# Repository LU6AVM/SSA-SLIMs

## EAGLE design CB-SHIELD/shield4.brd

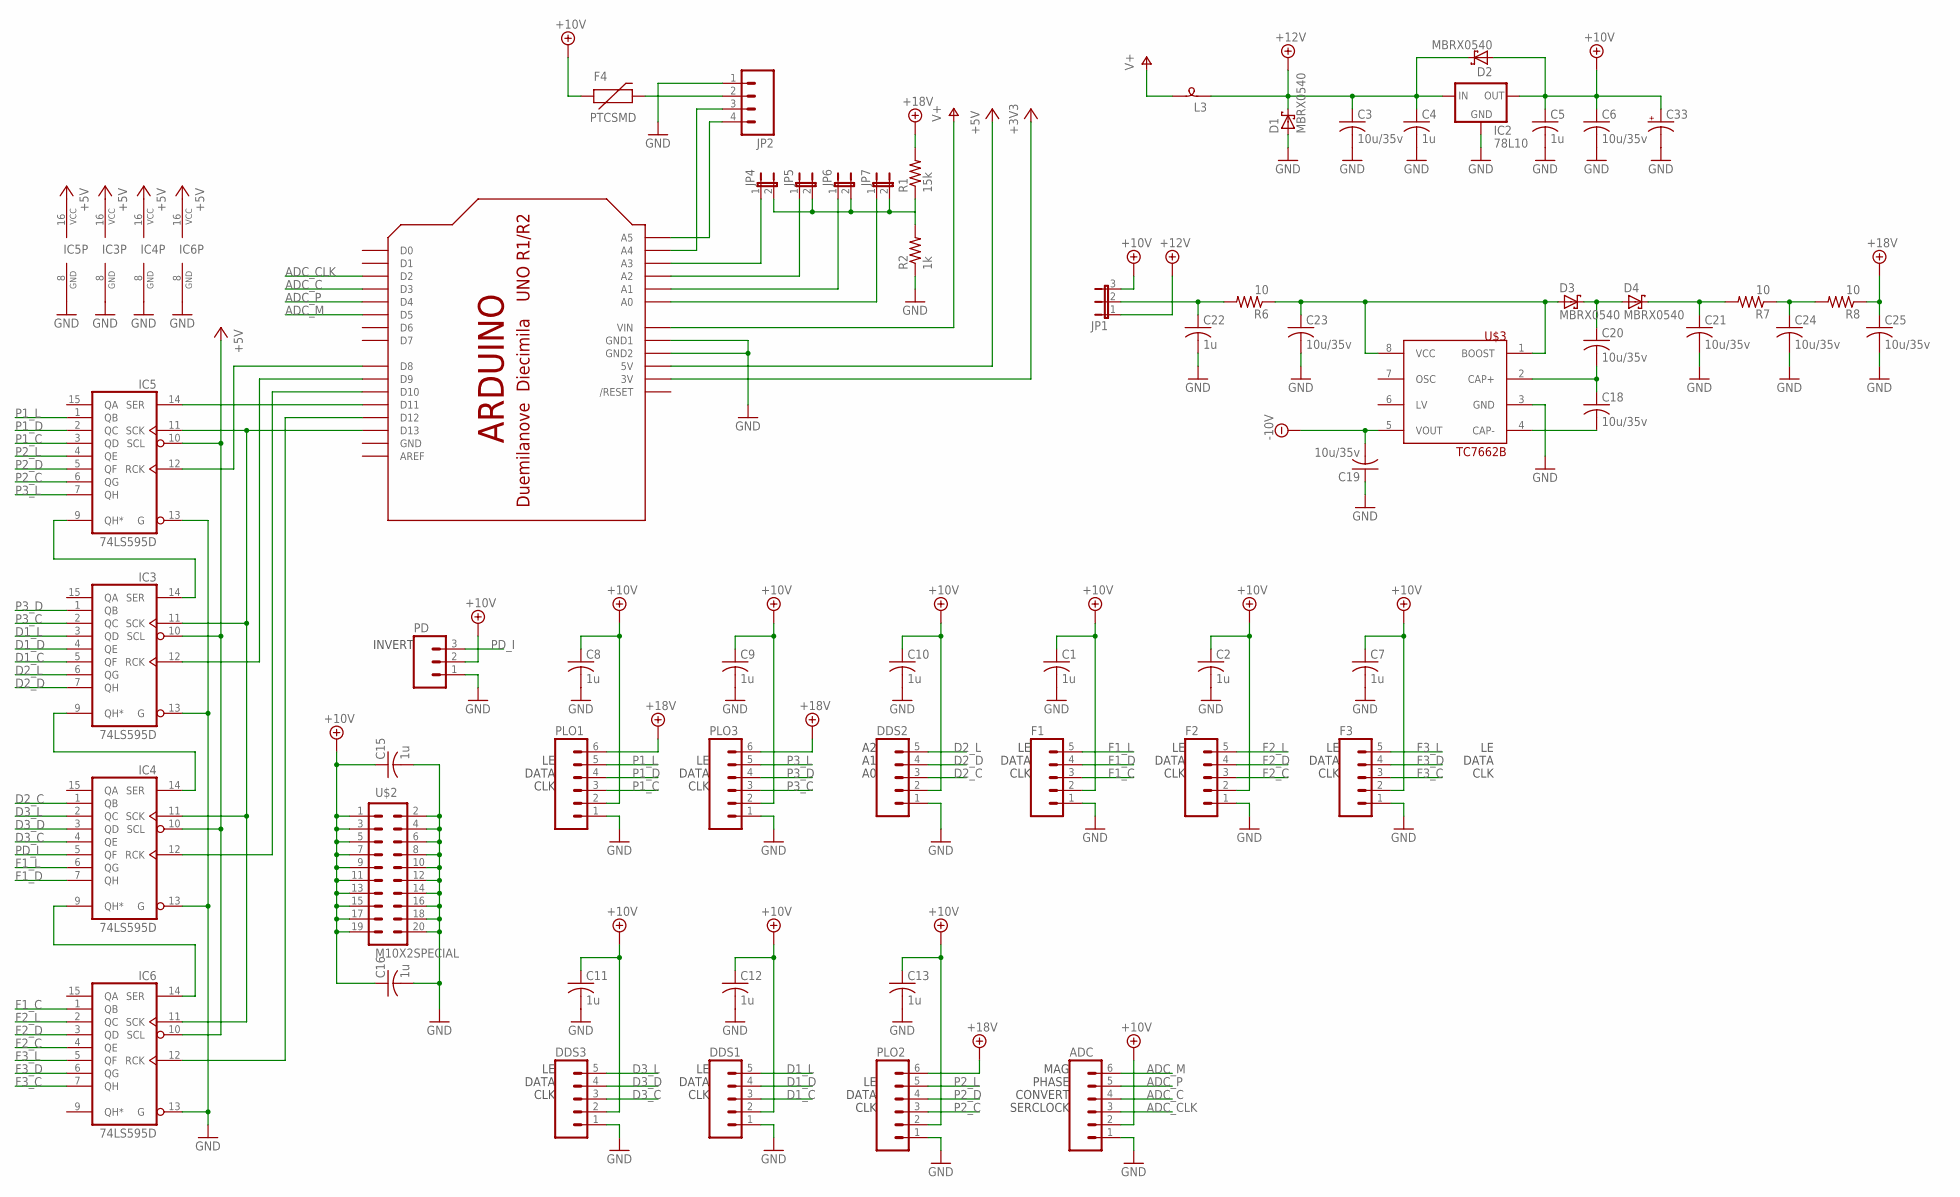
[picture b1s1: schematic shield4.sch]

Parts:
ADC: M06LOCK; 1X06_LOCK
C1, C2, C4, C5, C7, C8, C9, C10, C11, C12, C13, C15, C16, C22: 1u; C0603
C3, C6, C18, C19, C20, C21, C23, C24, C25: 10u/35v; C1206
C33: CPOL-USE2.5-6; E2,5-6
D1, D2, D3, D4: MBRX0540; SOD323-R
DDS1, DDS2, DDS3: M05LOCK; 1X05_LOCK
F1, F2, F3: M05LOCK; 1X05_LOCK
F4: PTCSMD; PTC-1206
IC2: 78L10; 78XXS
IC3, IC4, IC5, IC6: 74LS595D; SO16
JP1: JP2E; JP2
JP2: M04LOCK; 1X04_LOCK
JP4, JP5, JP6, JP7: JUMPER-2SMD-NO; SJ_2S-NO
L3: SM-B5
PD: M03LOCK; 1X03_LOCK
PLO1, PLO2, PLO3: M06LOCK; 1X06_LOCK
R1: 15k; R0603
R2: 1k; R0603
R6, R7, R8: 10; R0603
U$1: ARDUINO-NOHOLE
U$2: M10X2SPECIAL; 2X10_LOCK_SPECIAL
U$3: TC7662B; SO-08

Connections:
+3V3: U$1.3V
+5V: IC3.10 (SCL), IC3.16 (VCC), IC4.10 (SCL), IC4.16 (VCC), IC5.10 (SCL), IC5.16 (VCC), IC6.10 (SCL), IC6.16 (VCC), U$1.5V
+10V: ADC.2, C1.1, C2.1, C5.1, C6.1, C7.1, C8.1, C9.1, C10.1, C11.1, C12.1, C13.1, C15.1, C16.1, C33.+, D2.A, DDS1.2, DDS2.2, DDS3.2, F1.2, F2.2, F3.2, F4.1, IC2.OUT, JP1.3, PD.2, PLO1.2, PLO2.2, PLO3.2, U$2.1, U$2.3, U$2.5, U$2.7, U$2.9, U$2.11, U$2.13, U$2.15, U$2.17, U$2.19
+12V: C3.1, C4.1, D1.C, D2.C, IC2.IN, JP1.1, L3.1
+18V: C25.1, PLO1.6, PLO2.6, PLO3.6, R1.2, R8.1
-10V: C19.2, U$3.5 (VOUT)
ADC_C: ADC.4, U$1.D3
ADC_CLK: ADC.3, U$1.D2
ADC_M: ADC.6, U$1.D5
ADC_P: ADC.5, U$1.D4
D1_C: DDS1.3, IC3.5 (QF)
D1_D: DDS1.4, IC3.4 (QE)
D1_L: DDS1.5, IC3.3 (QD)
D2_C: DDS2.3, IC4.1 (QB)
D2_D: DDS2.4, IC3.7 (QH)
D2_L: DDS2.5, IC3.6 (QG)
D3_C: DDS3.3, IC4.4 (QE)
D3_D: DDS3.4, IC4.3 (QD)
D3_L: DDS3.5, IC4.2 (QC)
F1_C: F1.3, IC6.1 (QB)
F1_D: F1.4, IC4.7 (QH)
F1_L: F1.5, IC4.6 (QG)
F2_C: F2.3, IC6.4 (QE)
F2_D: F2.4, IC6.3 (QD)
F2_L: F2.5, IC6.2 (QC)
F3_C: F3.3, IC6.7 (QH)
F3_D: F3.4, IC6.6 (QG)
F3_L: F3.5, IC6.5 (QF)
GND: ADC.1, C1.2, C2.2, C3.2, C4.2, C5.2, C6.2, C7.2, C8.2, C9.2, C10.2, C11.2, C12.2, C13.2, C15.2, C16.2, C19.1, C21.2, C22.2, C23.2, C24.2, C25.2, C33.-, D1.A, DDS1.1, DDS2.1, DDS3.1, F1.1, F2.1, F3.1, IC2.GND, IC3.8 (GND), IC3.13 (G), IC4.8 (GND), IC4.13 (G), IC5.8 (GND), IC5.13 (G), IC6.8 (GND), IC6.13 (G), JP2.1, PD.1, PLO1.1, PLO2.1, PLO3.1, R2.1, U$1.GND, U$1.GND1, U$1.GND2, U$2.2, U$2.4, U$2.6, U$2.8, U$2.10, U$2.12, U$2.14, U$2.16, U$2.18, U$2.20, U$3.3 (GND)
unnamed: IC5.14 (SER), U$1.D11
unnamed: IC3.11 (SCK), IC4.11 (SCK), IC5.11 (SCK), IC6.11 (SCK), U$1.D13
unnamed: IC5.12 (RCK), U$1.D8
unnamed: IC3.14 (SER), IC5.9 (QH*)
unnamed: IC3.9 (QH*), IC4.14 (SER)
unnamed: IC4.9 (QH*), IC6.14 (SER)
unnamed: JP2.3, U$1.A4
unnamed: JP2.4, U$1.A5
unnamed: F4.2, JP2.2
unnamed: JP4.1, U$1.A3
unnamed: JP5.1, U$1.A2
unnamed: JP6.1, U$1.A1
unnamed: JP7.1, U$1.A0
unnamed: JP4.2, JP5.2, JP6.2, JP7.2, R1.1, R2.2
unnamed: IC6.12 (RCK), U$1.D12
unnamed: IC4.12 (RCK), U$1.D10
unnamed: IC3.12 (RCK), U$1.D9
unnamed: C22.1, JP1.2, R6.2
unnamed: C23.1, D3.A, R6.1, U$3.1 (BOOST), U$3.8 (VCC)
unnamed: C18.2, U$3.4 (CAP-)
unnamed: C18.1, C20.2, U$3.2 (CAP+)
unnamed: C20.1, D3.C, D4.A
unnamed: C21.1, D4.C, R7.2
unnamed: C24.1, R7.1, R8.2
P1_C: IC5.3 (QD), PLO1.3
P1_D: IC5.2 (QC), PLO1.4
P1_L: IC5.1 (QB), PLO1.5
P2_C: IC5.6 (QG), PLO2.3
P2_D: IC5.5 (QF), PLO2.4
P2_L: IC5.4 (QE), PLO2.5
P3_C: IC3.2 (QC), PLO3.3
P3_D: IC3.1 (QB), PLO3.4
P3_L: IC5.7 (QH), PLO3.5
PD_I: IC4.5 (QF), PD.3
V+: L3.2, U$1.VIN

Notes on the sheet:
SERCLOCK
CONVERT
PHASE
MAG
CLK
DATA
INVERT

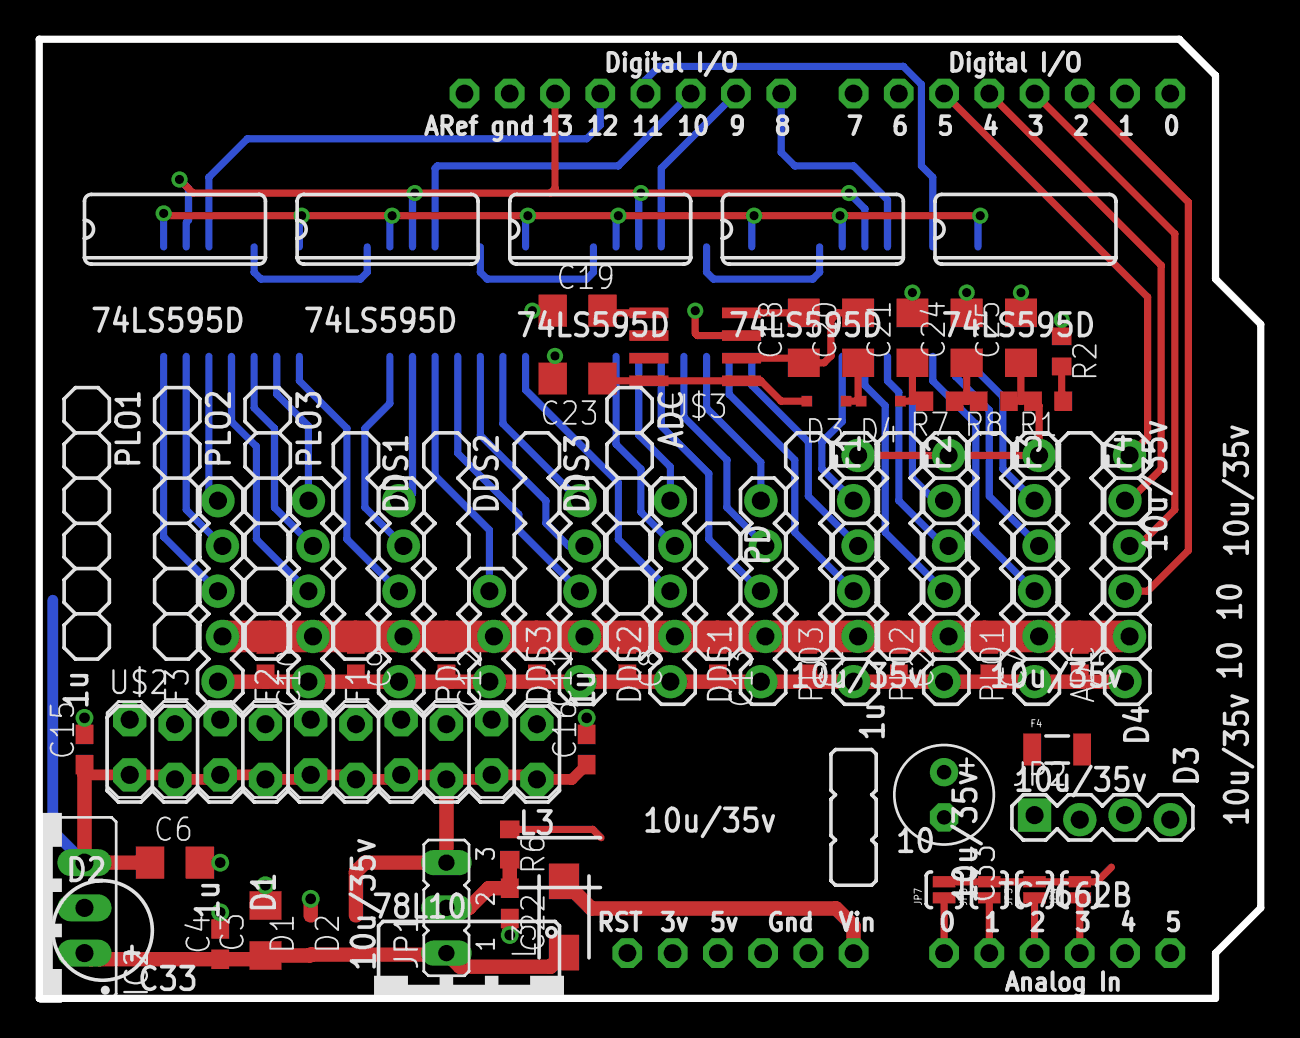
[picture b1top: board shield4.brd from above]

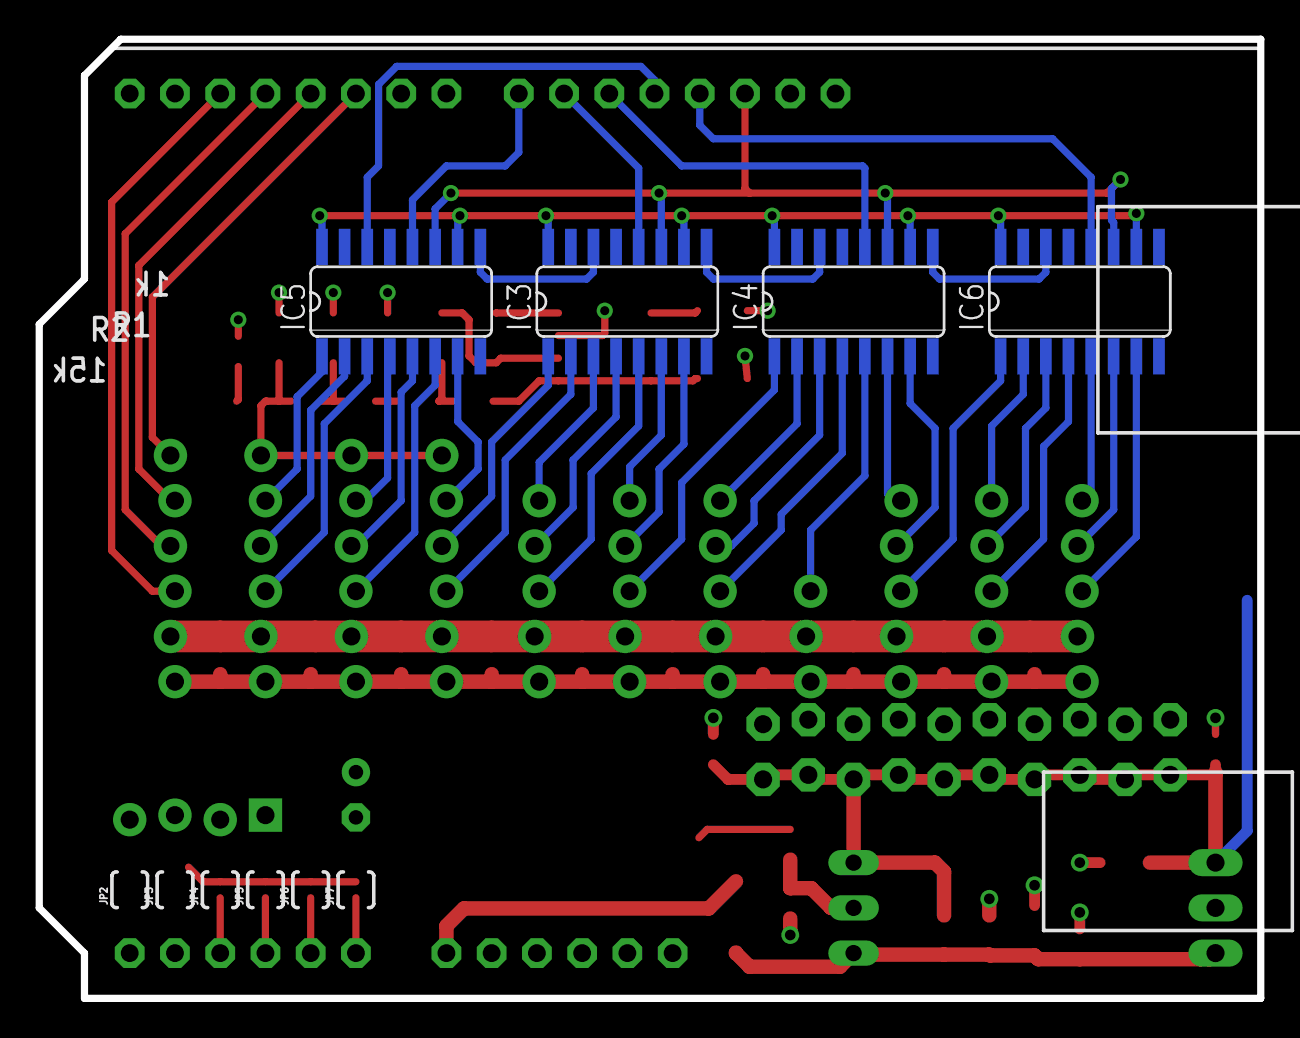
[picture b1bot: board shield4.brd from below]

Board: 2 copper layers, 68.6 x 53.8 mm, 60 parts (4 on the bottom side), 63 nets.

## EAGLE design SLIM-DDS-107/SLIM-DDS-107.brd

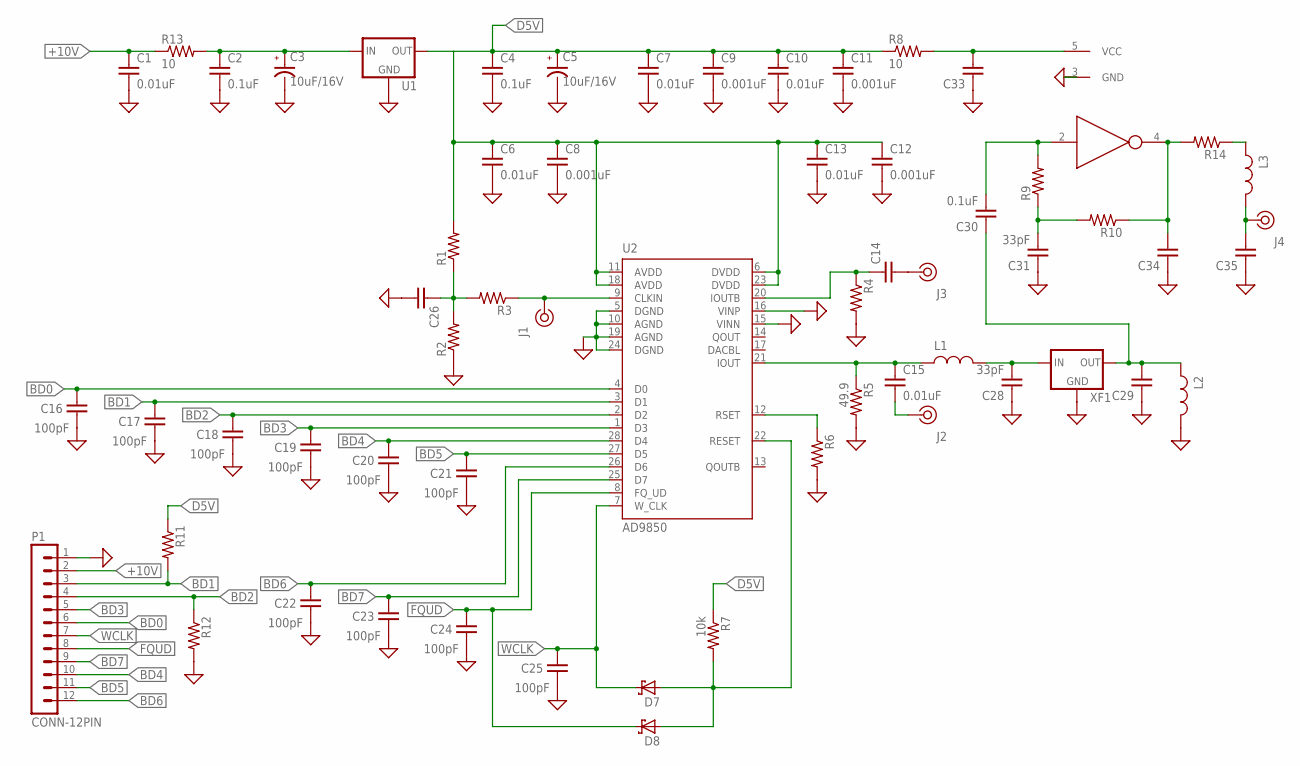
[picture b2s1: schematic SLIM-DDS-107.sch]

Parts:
C1, C6, C7, C10, C13, C15: 0.01uF; 0805
C2, C4, C30: 0.1uF; 0805
C3, C5: 10uF/16V; EIA3216
C8, C9, C11, C12: 0.001uF; 0805
C14, C26, C29, C33, C34, C35: CAP0805; 0805
C16, C17, C18, C19, C20, C21, C22, C23, C24, C25: 100pF; 0805
C28, C31: 33pF; 0805
D7, D8: SCHOTTKY-DIODE-SOD323; SOD323
J1, J2, J3, J4: COAX; SLIM_COAX_PAD
L1, L2, L3: INDUCTOR0805; 0805-IND
P1: CONN-12PIN
R1, R2, R3, R4, R6, R9, R10, R11, R12, R14: RESISTOR0805; 0805
R5: 49.9; 0805
R7: 10k; 0805
R8, R13: 10; 0805
U1: 78MXXLDPAK; TO252
U2: AD9850; SSOP28
U$1: 7SZ04SOT-23; SOT23-5L
XF1: XTALFILTER

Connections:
+10V: C1.1, P1.2, R13.1
BD0: C16.2, P1.6, U2.4 (D0)
BD1: C17.2, P1.3, R11.2, U2.3 (D1)
BD2: C18.2, P1.4, R12.1, U2.2 (D2)
BD3: C19.2, P1.5, U2.1 (D3)
BD4: C20.2, P1.10, U2.28 (D4)
BD5: C21.2, P1.11, U2.27 (D5)
BD6: C22.2, P1.12, U2.26 (D6)
BD7: C23.2, P1.9, U2.25 (D7)
D5V: C4.1, C5.A (+), C6.1, C7.1, C8.1, C9.1, C10.1, C11.1, C12.1, C13.1, R1.2, R7.1, R8.1, R11.1, U1.2 (OUT), U2.6 (DVDD), U2.11 (AVDD), U2.18 (AVDD), U2.23 (DVDD)
FQUD: C24.2, D8.C, P1.8, U2.8 (FQ_UD)
GND: C1.2, C2.2, C3.C (-), C4.2, C5.C (-), C6.2, C7.2, C8.2, C9.2, C10.2, C11.2, C12.2, C13.2, C16.1, C17.1, C18.1, C19.1, C20.1, C21.1, C22.1, C23.1, C24.1, C25.1, C26.2, C28.1, C29.1, C31.1, C33.1, C34.1, C35.1, J1.P$2 (GND), J2.P$2 (GND), J3.P$2 (GND), J4.P$2 (GND), L2.2, P1.1, R2.1, R4.2, R5.2, R6.2, R12.2, U1.3 (GND), U2.5 (DGND), U2.10 (AGND), U2.15 (VINN), U2.16 (VINP), U2.19 (AGND), U2.24 (DGND), U$1.3 (GND), XF1.3 (GND)
unnamed: C2.1, C3.A (+), R13.2, U1.1 (IN)
unnamed: C33.2, R8.2, U$1.5 (VCC)
unnamed: C26.1, R1.1, R2.2, R3.2
unnamed: J1.P$1 (1), R3.1, U2.9 (CLKIN)
unnamed: D7.A, D8.A, R7.2, U2.22 (RESET)
unnamed: C15.1, L1.1, R5.1, U2.21 (IOUT)
unnamed: R6.1, U2.12 (RSET)
unnamed: C15.2, J2.P$1 (1)
unnamed: C14.1, R4.1, U2.20 (IOUTB)
unnamed: C34.2, R10.1, R14.2, U$1.4 (OUT)
unnamed: C31.2, R9.1, R10.2
unnamed: L3.1, R14.1
unnamed: C35.2, J4.P$1 (1), L3.2
unnamed: C28.2, L1.2, XF1.2 (IN)
unnamed: C29.2, C30.1, L2.1, XF1.1 (OUT)
unnamed: C30.2, R9.2, U$1.2 (IN)
unnamed: C14.2, J3.P$1 (1)
WCLK: C25.2, D7.C, P1.7, U2.7 (W_CLK)

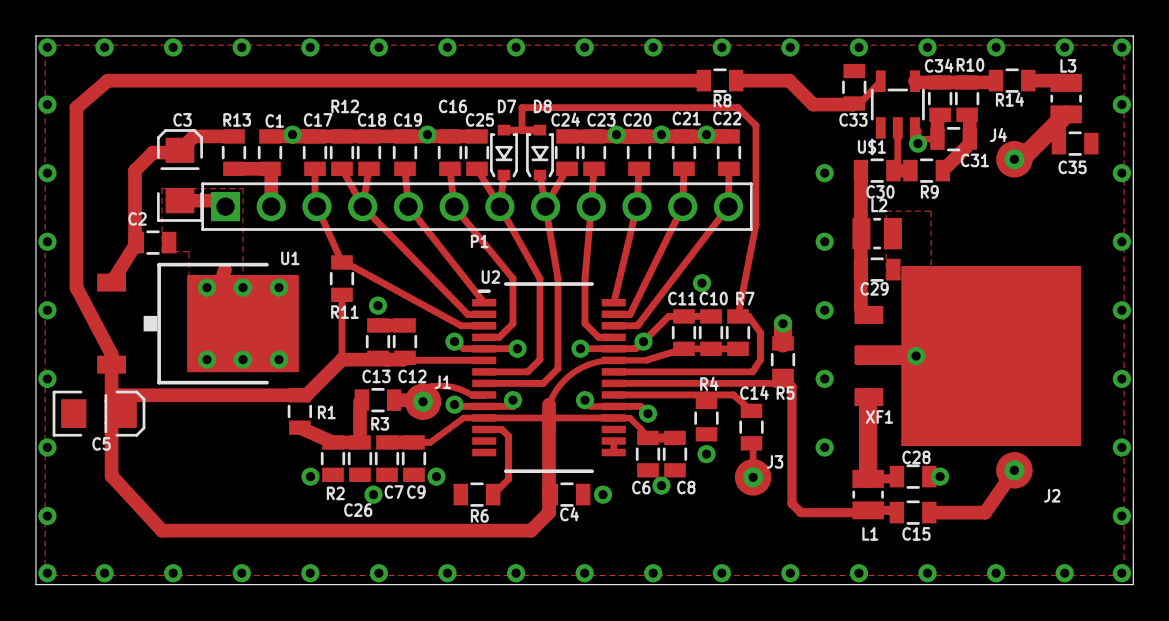
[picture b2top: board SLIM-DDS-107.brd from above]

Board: 2 copper layers, 61.0 x 30.5 mm, 61 parts (0 on the bottom side), 30 nets.

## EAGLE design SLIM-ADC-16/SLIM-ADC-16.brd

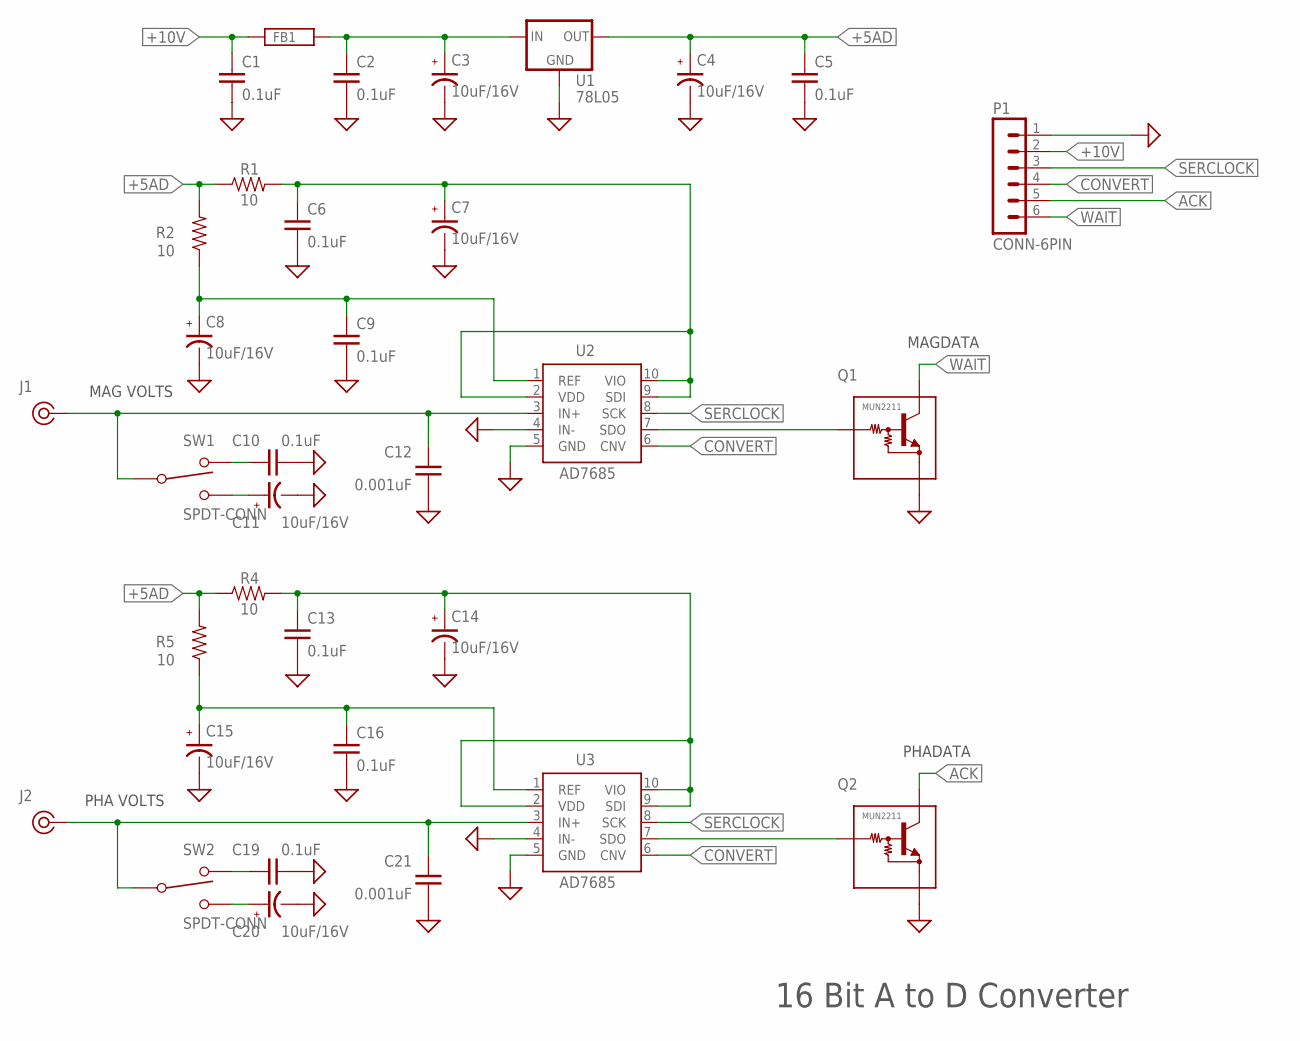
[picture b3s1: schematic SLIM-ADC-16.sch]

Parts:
C1, C2, C5, C6, C9, C10, C13, C16, C19: 0.1uF; 0805
C3, C4, C7, C8, C11, C14, C15, C20: 10uF/16V; EIA3216
C12, C21: 0.001uF; 0805
FB1: FERRITE0805; 0805
J1, J2: COAX; SLIM_COAX_PAD
P1: CONN-6PIN
Q1, Q2: MUN2211; SOT23
R1, R2, R4, R5: 10; 0805
SW1, SW2: SPDT-CONN; CONN-3PIN
U1: 78L05; SOT89
U2, U3: AD7685; MSOP10

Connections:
+5AD: C4.A (+), C5.1, R1.1, R2.2, R4.1, R5.2, U1.1 (OUT)
+10V: C1.1, FB1.1, P1.2
ACK: P1.5, Q2.C
CONVERT: P1.4, U2.6 (CNV), U3.6 (CNV)
GND: C1.2, C2.2, C3.C (-), C4.C (-), C5.2, C6.2, C7.C (-), C8.C (-), C9.2, C10.2, C11.C (-), C12.2, C13.2, C14.C (-), C15.C (-), C16.2, C19.2, C20.C (-), C21.2, J1.P$2 (GND), J2.P$2 (GND), P1.1, Q1.E, Q2.E, U1.2 (GND), U1.4 (GND), U2.4 (IN-), U2.5 (GND), U3.4 (IN-), U3.5 (GND)
unnamed: C8.A (+), C9.1, R2.1, U2.1 (REF)
unnamed: C6.1, C7.A (+), R1.2, U2.2 (VDD), U2.9 (SDI), U2.10 (VIO)
unnamed: C12.1, J1.P$1 (1), SW1.2, U2.3 (IN+)
unnamed: C10.1, SW1.1
unnamed: C11.A (+), SW1.3
unnamed: Q1.B, U2.7 (SDO)
unnamed: C2.1, C3.A (+), FB1.2, U1.3 (IN)
unnamed: C15.A (+), C16.1, R5.1, U3.1 (REF)
unnamed: C13.1, C14.A (+), R4.2, U3.2 (VDD), U3.9 (SDI), U3.10 (VIO)
unnamed: C21.1, J2.P$1 (1), SW2.2, U3.3 (IN+)
unnamed: C19.1, SW2.1
unnamed: C20.A (+), SW2.3
unnamed: Q2.B, U3.7 (SDO)
SERCLOCK: P1.3, U2.8 (SCK), U3.8 (SCK)
WAIT: P1.6, Q1.C

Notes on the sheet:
MAGDATA
PHADATA
MAG VOLTS
PHA VOLTS
16 Bit A to D Converter

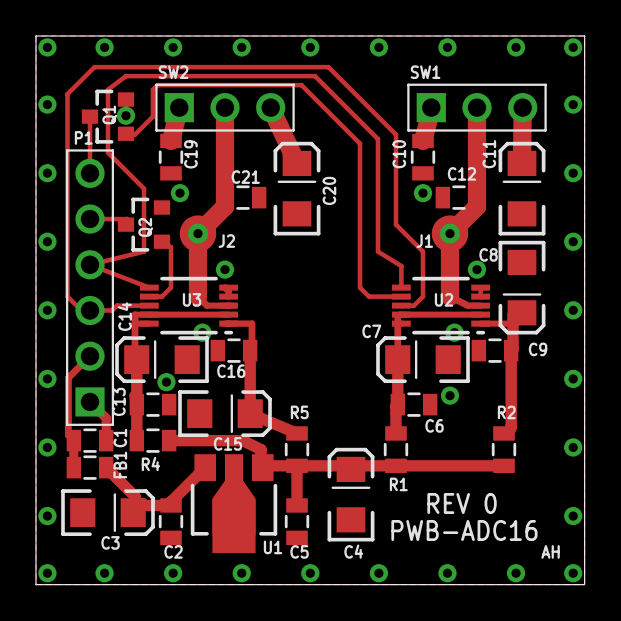
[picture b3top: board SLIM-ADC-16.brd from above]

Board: 2 copper layers, 30.5 x 30.5 mm, 34 parts (0 on the bottom side), 20 nets.

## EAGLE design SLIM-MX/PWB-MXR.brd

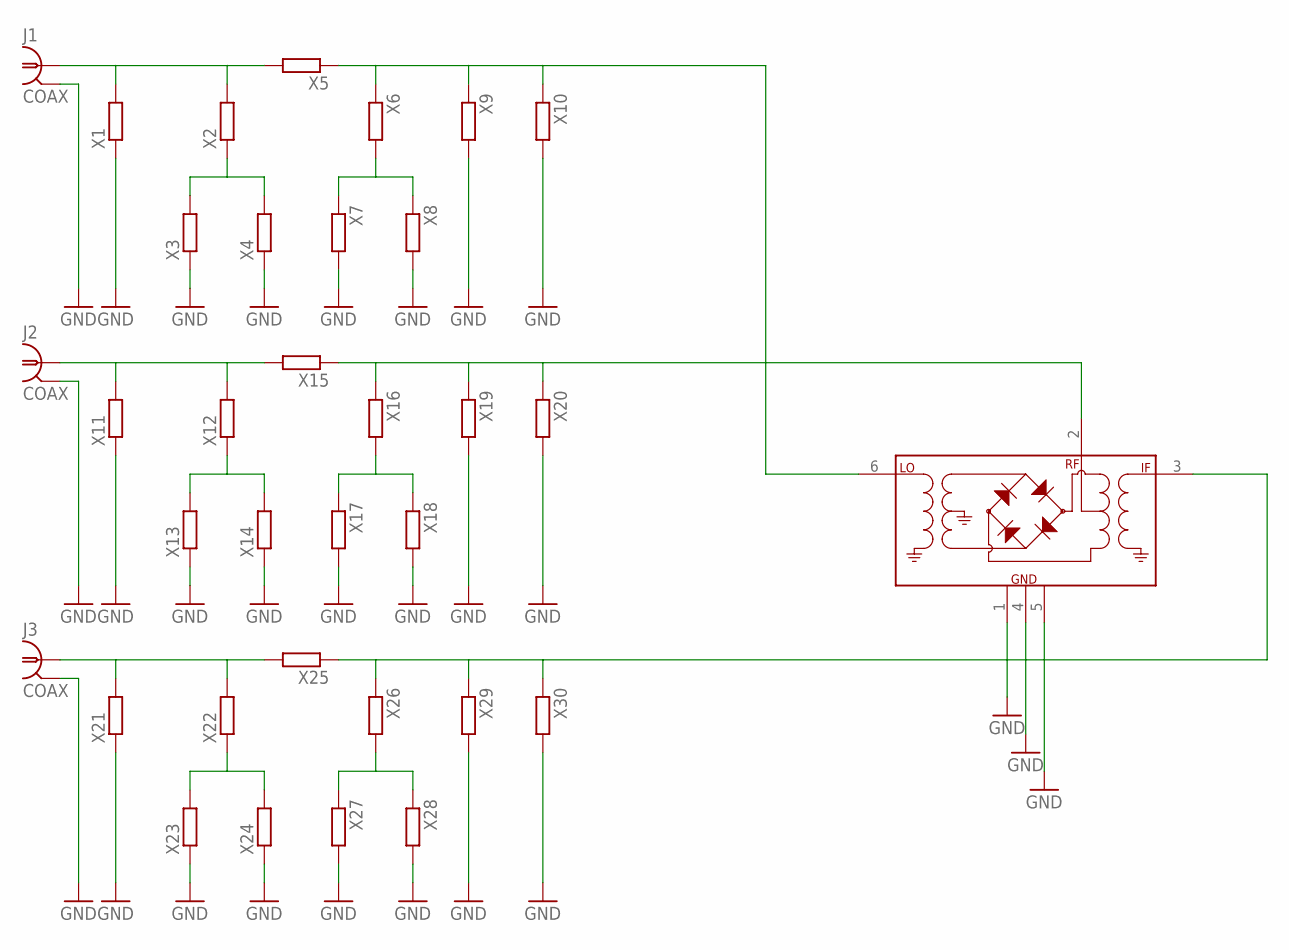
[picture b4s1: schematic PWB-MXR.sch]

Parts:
J1, J2, J3: COAX; SLIM_COAX_PAD
U$1: ADE-11X; CD542
X1, X2, X3, X4, X5, X6, X7, X8, X9, X10, X11, X12, X13, X14, X15, X16, X17, X18, X19, X20, X21, X22, X23, X24, X25, X26, X27, X28, X29, X30: R-EU_M0805; M0805

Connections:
GND: J1.P$2 (GND), J2.P$2 (GND), J3.P$2 (GND), U$1.1 (GND), U$1.4 (GND), U$1.5 (GND), X1.1, X3.1, X4.1, X7.2, X8.2, X9.2, X10.2, X11.1, X13.1, X14.1, X17.2, X18.2, X19.2, X20.2, X21.1, X23.1, X24.1, X27.2, X28.2, X29.2, X30.2
unnamed: J1.P$1 (1), X1.2, X2.2, X5.2
unnamed: U$1.6 (LO), X5.1, X6.1, X9.1, X10.1
unnamed: X2.1, X3.2, X4.2
unnamed: X6.2, X7.1, X8.1
unnamed: J2.P$1 (1), X11.2, X12.2, X15.2
unnamed: U$1.2 (RF), X15.1, X16.1, X19.1, X20.1
unnamed: X12.1, X13.2, X14.2
unnamed: X16.2, X17.1, X18.1
unnamed: J3.P$1 (1), X21.2, X22.2, X25.2
unnamed: U$1.3 (IF), X25.1, X26.1, X29.1, X30.1
unnamed: X22.1, X23.2, X24.2
unnamed: X26.2, X27.1, X28.1

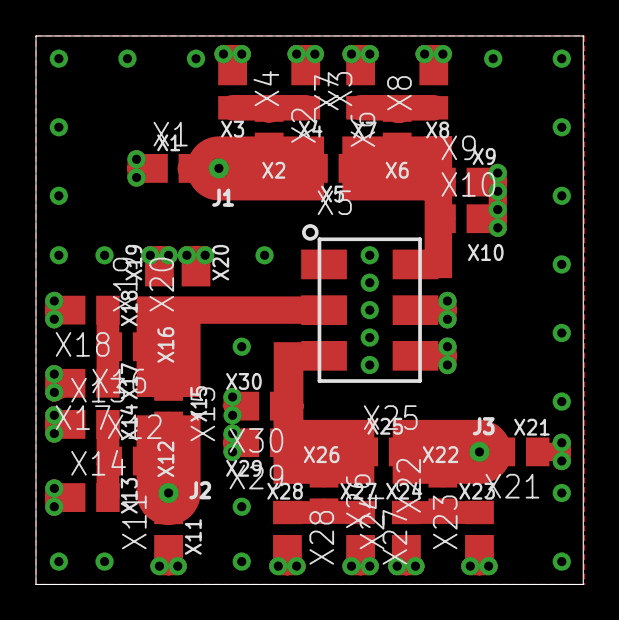
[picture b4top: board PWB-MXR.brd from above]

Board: 2 copper layers, 30.4 x 30.5 mm, 34 parts (0 on the bottom side), 13 nets.

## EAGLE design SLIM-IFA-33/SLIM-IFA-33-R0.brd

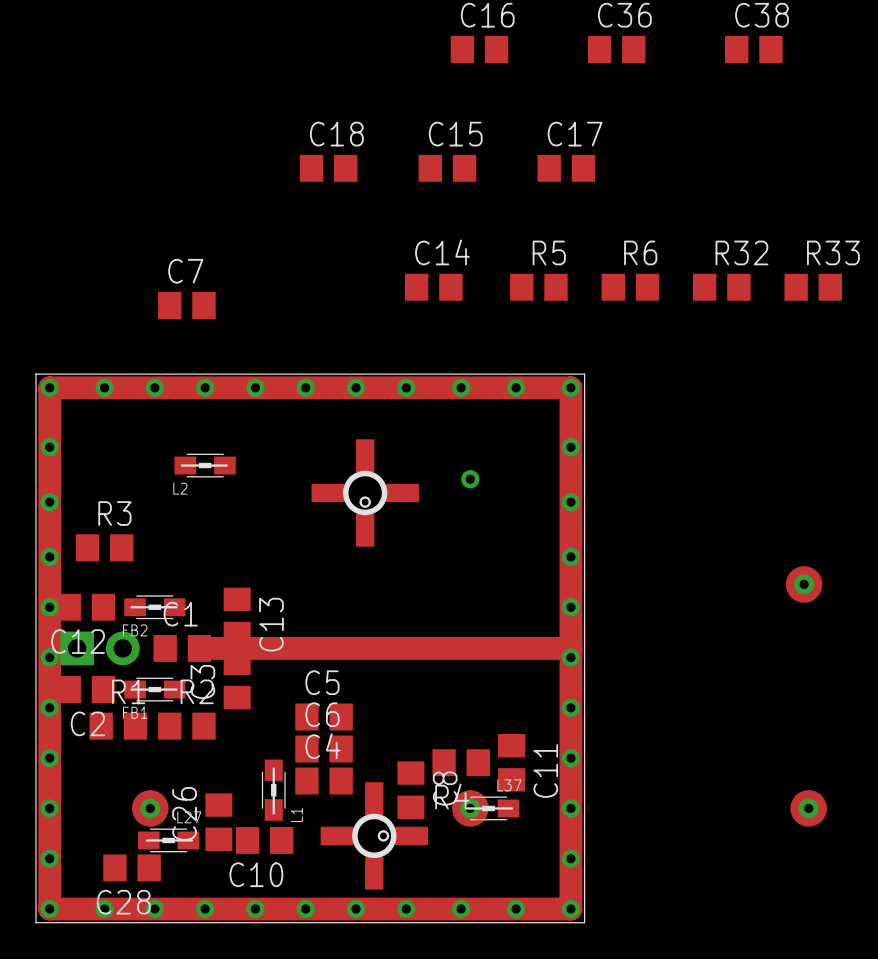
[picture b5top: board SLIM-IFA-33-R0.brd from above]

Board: 2 copper layers, 30.5 x 30.5 mm, 42 parts (1 on the bottom side), 22 nets.

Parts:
C1, C7, C8, C17, C18: .01uF; C0805
C2, C3, C4, C12, C13, C14: .1uF; C0805
C5, C15: 10uF; C0805
C6, C16, C26, C28, C36, C38: 100pF; C0805
C10, C11: 1000pF; C0805
FB1, FB2: 0805
J1, J2, J4, J5: COAX; SLIM_COAX_PAD
JP1: MOLEX-1X2
L1, L2: 3.3uH; 0805
L27, L37: 330nH; 0805
R1, R2, R5, R6: 75; R0805
R3, R4, R32, R33: 0; R0805
U1, U2: ERA-33; WW107

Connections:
GND: C1.2, C2.2, C3.2, C4.2, C5.2, C6.2, C7.2, C12.2, C13.2, C14.2, C15.2, C16.2, C17.2, C26.2, C28.2, C36.2, C38.2, J1.P$2, J2.P$2, J4.P$2, J5.P$2, JP1.1, U1.P$2, U1.P$4
unnamed: C2.1, FB1.1, R1.1
unnamed: C3.1, R1.2, R2.1
unnamed: C4.1, C5.1, C6.1, C7.1, L1.2, R2.2
unnamed: J4.P$1, R3.1
unnamed: R3.2, R4.1
unnamed: C8.1, R4.2
unnamed: C10.1, L1.1, U1.P$3
unnamed: C10.2, C26.1, L27.1
unnamed: C28.1, J5.P$1, L27.2
unnamed: C8.2, U1.P$1
unnamed: C12.1, FB2.1, R5.1
unnamed: C13.1, R5.2, R6.1
unnamed: C14.1, C15.1, C16.1, C17.1, L2.2, R6.2
unnamed: J1.P$1, R32.1
unnamed: R32.2, R33.1
unnamed: C18.1, R33.2
unnamed: C11.1, L2.1, U2.P$3
unnamed: C11.2, C36.1, L37.1
unnamed: C38.1, J2.P$1, L37.2
unnamed: C18.2, U2.P$1
VCC: C1.1, FB1.2, FB2.2, JP1.2

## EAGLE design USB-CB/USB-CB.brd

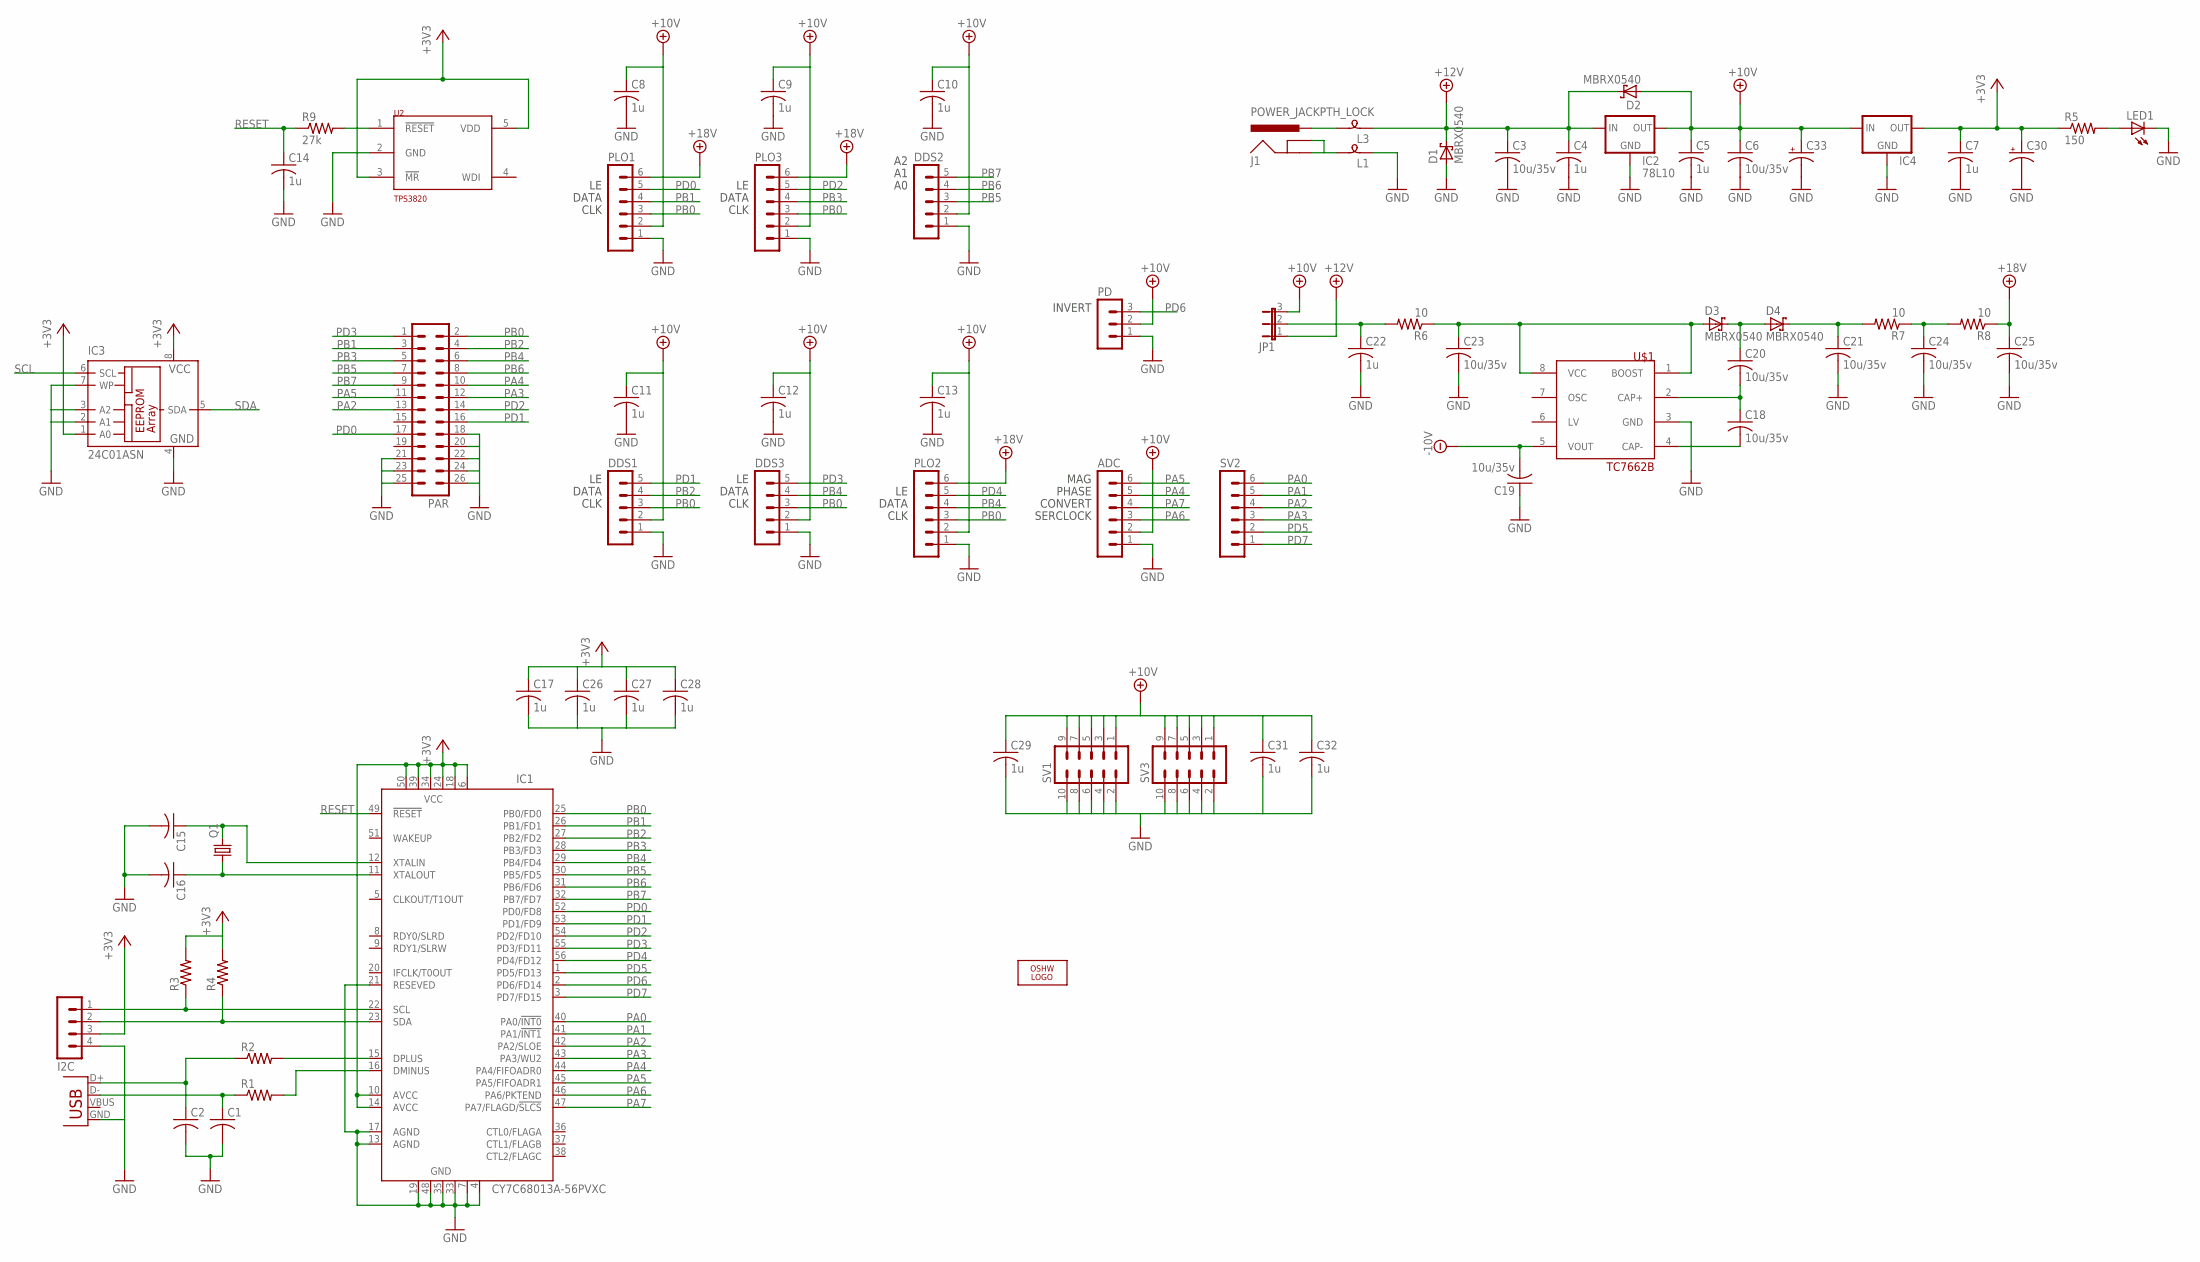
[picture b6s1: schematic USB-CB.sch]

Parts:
ADC: MA06-1
C1, C2, C15, C16: C-USC0603; C0603
C3, C6, C18, C19, C20, C21, C23, C24, C25: 10u/35v; C1206
C4, C5, C7, C8, C9, C10, C11, C12, C13, C14, C17, C22, C26, C27, C28, C29, C31, C32: 1u; C0603
C30, C33: CPOL-USE2.5-6; E2,5-6
D1, D2, D3, D4: MBRX0540; SOD323-R
DDS1, DDS2, DDS3: MA05-1
I2C: MA04-1
IC1: CY7C68013A-56PVXC; SSOP56
IC2: 78L10; 78XXS
IC3: 24C01ASN; SO-08
IC4: 78LXXAC; SOT89R
J1: POWER_JACKPTH_LOCK; POWER_JACK_PTH_LOCK
JP1: JP2E; JP2
L1, L3: SM-B5
LED1: LED5MM
LOGO1: OSHW_LOGO_FILLX0200-NT; OSHW_FILLX200_NOTEXT
PAR: MA13-2
PD: MA03-1
PLO1, PLO2, PLO3: MA06-1
Q1: CRYSTALHC49S; HC49/S
R1, R2, R3, R4: R-US_R0603; R0603
R5: 150; R0603
R6, R7, R8: 10; R0603
R9: 27k; R0603
SV1, SV3: MA05-2PIN; MA05-2
SV2: MA06-1
U2: TPS3820; SC74_INFINEON
U$1: TC7662B; SO-08
X1: USBSMD; USB-MINIB

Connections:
+3V3: C7.1, C17.1, C26.1, C27.1, C28.1, C30.+, I2C.3, IC1.6 (VCC), IC1.10 (AVCC), IC1.14 (AVCC), IC1.18 (VCC), IC1.24 (VCC), IC1.34 (VCC), IC1.39 (VCC), IC1.50 (VCC), IC3.1 (A0), IC3.8 (VCC), IC4.3 (OUT), R3.2, R4.2, R5.1, U2.3 (!MR), U2.5 (VDD)
+10V: ADC.2, C5.1, C6.1, C8.1, C9.1, C10.1, C11.1, C12.1, C13.1, C29.1, C31.1, C32.1, C33.+, D2.A, DDS1.2, DDS2.2, DDS3.2, IC2.OUT, IC4.1 (IN), JP1.3, PD.2, PLO1.2, PLO2.2, PLO3.2, SV1.1, SV1.3, SV1.5, SV1.7, SV1.9, SV3.1, SV3.3, SV3.5, SV3.7, SV3.9
+12V: C3.1, C4.1, D1.C, D2.C, IC2.IN, JP1.1, L3.1
+18V: C25.1, PLO1.6, PLO2.6, PLO3.6, R8.1
-10V: C19.2, U$1.5 (VOUT)
GND: ADC.1, C1.2, C2.2, C3.2, C4.2, C5.2, C6.2, C7.2, C8.2, C9.2, C10.2, C11.2, C12.2, C13.2, C14.2, C15.2, C16.2, C17.2, C19.1, C21.2, C22.2, C23.2, C24.2, C25.2, C26.2, C27.2, C28.2, C29.2, C30.-, C31.2, C32.2, C33.-, D1.A, DDS1.1, DDS2.1, DDS3.1, I2C.4, IC1.4 (GND), IC1.7 (GND), IC1.13 (AGND), IC1.17 (AGND), IC1.19 (GND), IC1.21 (RESEVED), IC1.33 (GND), IC1.35 (GND), IC1.48 (GND), IC2.GND, IC3.2 (A1), IC3.3 (A2), IC3.4 (GND), IC3.7 (WP), IC4.2 (GND), L1.1, LED1.K (C), PAR.18, PAR.20, PAR.21, PAR.22, PAR.23, PAR.24, PAR.25, PAR.26, PD.1, PLO1.1, PLO2.1, PLO3.1, SV1.2, SV1.4, SV1.6, SV1.8, SV1.10, SV3.2, SV3.4, SV3.6, SV3.8, SV3.10, U2.2 (GND), U$1.3 (GND), X1.GND
unnamed: IC1.15 (DPLUS), R2.2
unnamed: IC1.16 (DMINUS), R1.2
unnamed: C1.1, R1.1, X1.D-
unnamed: C2.1, R2.1, X1.D+
unnamed: C22.1, JP1.2, R6.2
unnamed: C21.1, D4.C, R7.2
unnamed: C23.1, D3.A, R6.1, U$1.1 (BOOST), U$1.8 (VCC)
unnamed: C18.2, U$1.4 (CAP-)
unnamed: C18.1, C20.2, U$1.2 (CAP+)
unnamed: C20.1, D3.C, D4.A
unnamed: C24.1, R7.1, R8.2
unnamed: J1.GND, L1.2
unnamed: J1.PWR, L3.2
unnamed: R9.2, U2.1 (!RESET)
unnamed: C16.1, IC1.11 (XTALOUT), Q1.1
unnamed: C15.1, IC1.12 (XTALIN), Q1.2
unnamed: LED1.A, R5.2
PA0: IC1.40 (PA0/!INT0), SV2.6
PA1: IC1.41 (PA1/!INT1), SV2.5
PA2: IC1.42 (PA2/SLOE), PAR.13, SV2.4
PA3: IC1.43 (PA3/WU2), PAR.12, SV2.3
PA4: ADC.5, IC1.44 (PA4/FIFOADR0), PAR.10
PA5: ADC.6, IC1.45 (PA5/FIFOADR1), PAR.11
PA6: ADC.3, IC1.46 (PA6/PKTEND)
PA7: ADC.4, IC1.47 (PA7/FLAGD/!SLCS)
PB0: DDS1.3, DDS3.3, IC1.25 (PB0/FD0), PAR.2, PLO1.3, PLO2.3, PLO3.3
PB1: IC1.26 (PB1/FD1), PAR.3, PLO1.4
PB2: DDS1.4, IC1.27 (PB2/FD2), PAR.4
PB3: IC1.28 (PB3/FD3), PAR.5, PLO3.4
PB4: DDS3.4, IC1.29 (PB4/FD4), PAR.6, PLO2.4
PB5: DDS2.3, IC1.30 (PB5/FD5), PAR.7
PB6: DDS2.4, IC1.31 (PB6/FD6), PAR.8
PB7: DDS2.5, IC1.32 (PB7/FD7), PAR.9
PD0: IC1.52 (PD0/FD8), PAR.17, PLO1.5
PD1: DDS1.5, IC1.53 (PD1/FD9), PAR.16
PD2: IC1.54 (PD2/FD10), PAR.14, PLO3.5
PD3: DDS3.5, IC1.55 (PD3/FD11), PAR.1
PD4: IC1.56 (PD4/FD12), PLO2.5
PD5: IC1.1 (PD5/FD13), SV2.2
PD6: IC1.2 (PD6/FD14), PD.3
PD7: IC1.3 (PD7/FD15), SV2.1
RESET: C14.1, IC1.49 (!RESET), R9.1
SCL: I2C.1, IC1.22 (SCL), IC3.6 (SCL), R3.1
SDA: I2C.2, IC1.23 (SDA), IC3.5 (SDA), R4.1

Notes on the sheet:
SERCLOCK
CONVERT
PHASE
MAG
CLK
DATA
INVERT

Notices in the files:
USB-CB/USB-CB.brd:
Copyright William Dillon, July 2011
Licensed under the TAPR Open Hardware License
